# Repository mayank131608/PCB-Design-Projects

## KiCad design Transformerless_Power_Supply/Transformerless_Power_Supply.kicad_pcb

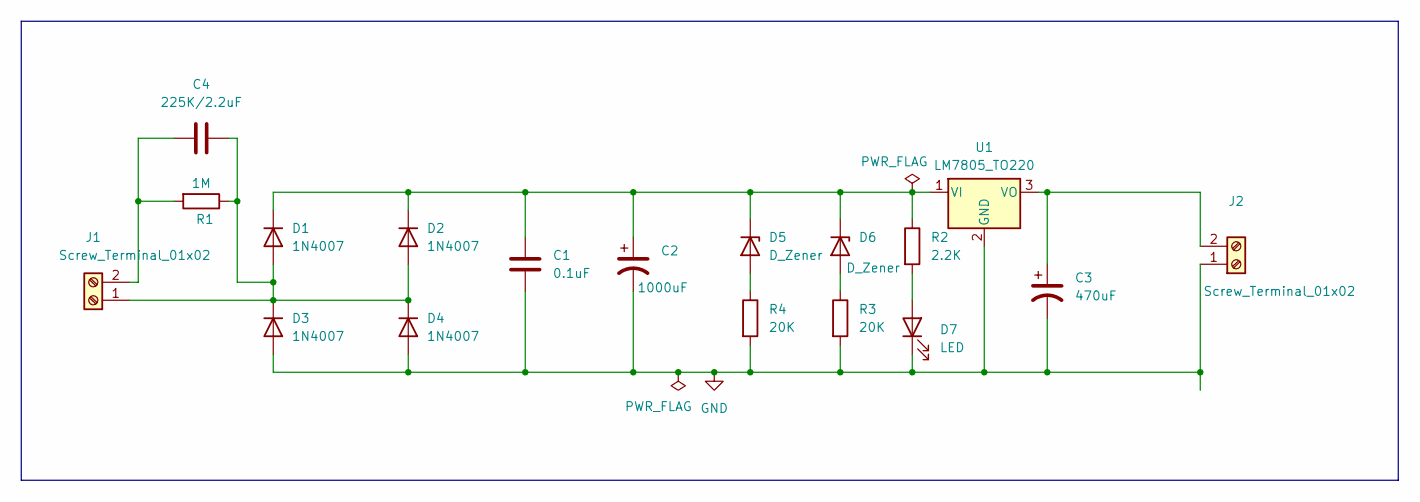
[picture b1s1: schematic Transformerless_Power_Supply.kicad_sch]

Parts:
C1: 0.1uF; C_Disc_D4.7mm_W2.5mm_P5.00mm
C2: 1000uF; CP_Radial_D10.0mm_P5.00mm
C3: 470uF; CP_Radial_D10.0mm_P3.80mm
C4: 225K/2.2uF; C_Rect_L18.0mm_W6.0mm_P15.00mm_FKS3_FKP3
D1, D2, D3, D4: 1N4007; D_DO-41_SOD81_P10.16mm_Horizontal
D5, D6: D_Zener; D_A-405_P7.62mm_Horizontal
D7: LED; LED_D5.0mm
J1, J2: Screw_Terminal_01x02; TerminalBlock_bornier-2_P5.08mm
R1: 1M; R_Axial_DIN0207_L6.3mm_D2.5mm_P7.62mm_Horizontal
R2: 2.2K; R_Axial_DIN0207_L6.3mm_D2.5mm_P7.62mm_Horizontal
R3, R4: 20K; R_Axial_DIN0207_L6.3mm_D2.5mm_P7.62mm_Horizontal
U1: LM7805_TO220; TO-220-3_Vertical

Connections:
GND: C1.2, C2.2, C3.2, D3.2 (A), D4.2 (A), D7.1 (K), J2.1, R3.2, R4.2, U1.2 (GND)
unnamed: C4.2, D1.2 (A), D2.2 (A), D3.1 (K), D4.1 (K), J1.1, R1.1
unnamed: C1.1, C2.1, D1.1 (K), D2.1 (K), D5.1 (K), D6.1 (K), R2.1, U1.1 (VI)
unnamed: D5.2 (A), R4.1
unnamed: D6.2 (A), R3.1
unnamed: D7.2 (A), R2.2
unnamed: C4.1, J1.2, R1.2
unnamed: C3.1, J2.2, U1.3 (VO)

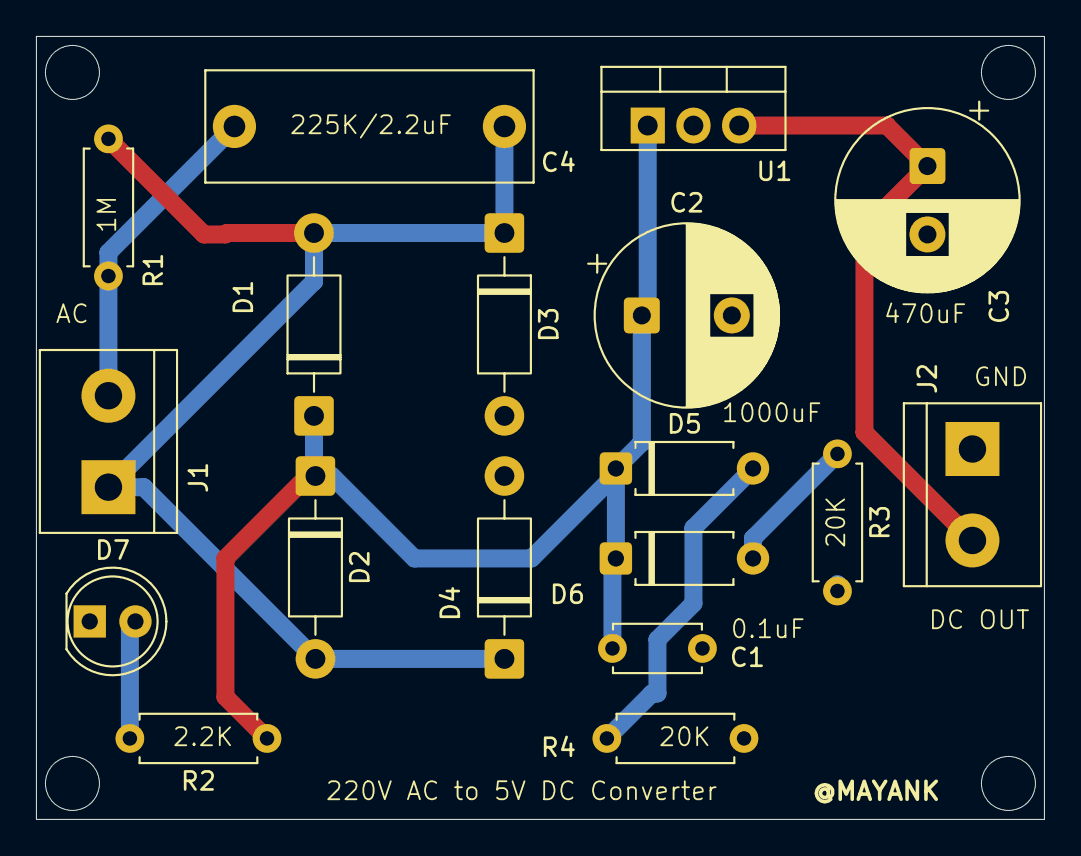
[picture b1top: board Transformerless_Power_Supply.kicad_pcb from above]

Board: 2 copper layers, 56.0 x 43.5 mm, 18 parts (0 on the bottom side), 8 nets.

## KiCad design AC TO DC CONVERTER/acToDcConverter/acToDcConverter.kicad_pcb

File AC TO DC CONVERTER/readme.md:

# AC to DC Converter PCB (Bridge Rectifier Power Supply)

A beginner-friendly PCB design of a **linear AC to DC power supply** created using KiCad.
This project converts low-voltage AC from a step-down transformer into filtered DC output using a full bridge rectifier and smoothing capacitor.

> ⚠️ This circuit is designed for transformer output (9–15VAC).
> **DO NOT connect directly to 230V mains.**

---

## 📌 Features

* Full bridge rectifier using 1N4007 diodes
* Ripple filtering using electrolytic capacitor
* Power indication LED
* Screw terminal input/output connectors
* Single layer PCB (easy to manufacture)
* 3D modeled board

---

## 🧠 Working Principle

1. AC voltage from a step-down transformer enters through input terminal
2. Four diodes form a bridge rectifier converting AC → pulsating DC
3. Electrolytic capacitor smooths ripple and produces DC
4. LED indicates output presence
5. DC available at output terminal

[
V_{DC} ≈ 1.414 × V_{AC(rms)} − 2V_d
]

Example:
12VAC → ~15–17V DC (no load)

---

## 🗂️ Files Included

| File       | Description         |
| ---------- | ------------------- |
| Schematic  | Circuit diagram     |
| PCB Layout | Routed PCB          |
| 3D Model   | Board preview       |
| Gerbers    | Manufacturing files |

---

## 🔧 Components Used

| Component | Value                         |
| --------- | ----------------------------- |
| D1–D4     | 1N4007 Diodes                 |
| C1        | 1000µF Electrolytic Capacitor |
| R1        | 10kΩ                          |
| R2        | 2.2kΩ                         |
| D5        | LED                           |
| J1, J2    | Screw Terminals               |

---

## 📤 Output Voltage

| AC Input | Approx DC Output |
| -------- | ---------------- |
| 9VAC     | ~12V             |
| 12VAC    | ~16V             |
| 15VAC    | ~20V             |

*(varies with load)*

---

## ⚠️ Safety

* Use **only transformer isolated AC**
* Do not connect mains supply
* Not a regulated power supply
* Output voltage changes with load

---

## 🛠️ Designed With

* KiCad (Schematic & PCB)
* KiCad 3D Viewer

---

## 🎯 Learning Objectives

This project helped me learn:

* Bridge rectifier design
* Capacitor filtering
* PCB routing for power circuits
* Footprints & 3D modeling
* Basic power electronics layout rules

---

## 🚀 Future Improvements

* Add voltage regulator (7805 / 7812)
* Add fuse protection
* Add reverse polarity protection
* Add heatsink support

---

## 👨‍💻 Author

**Mayank Pandey**, 
Electronics Engineering Student, 
HBTU KANPUR

---

⭐ If you found this useful, feel free to star the repository!

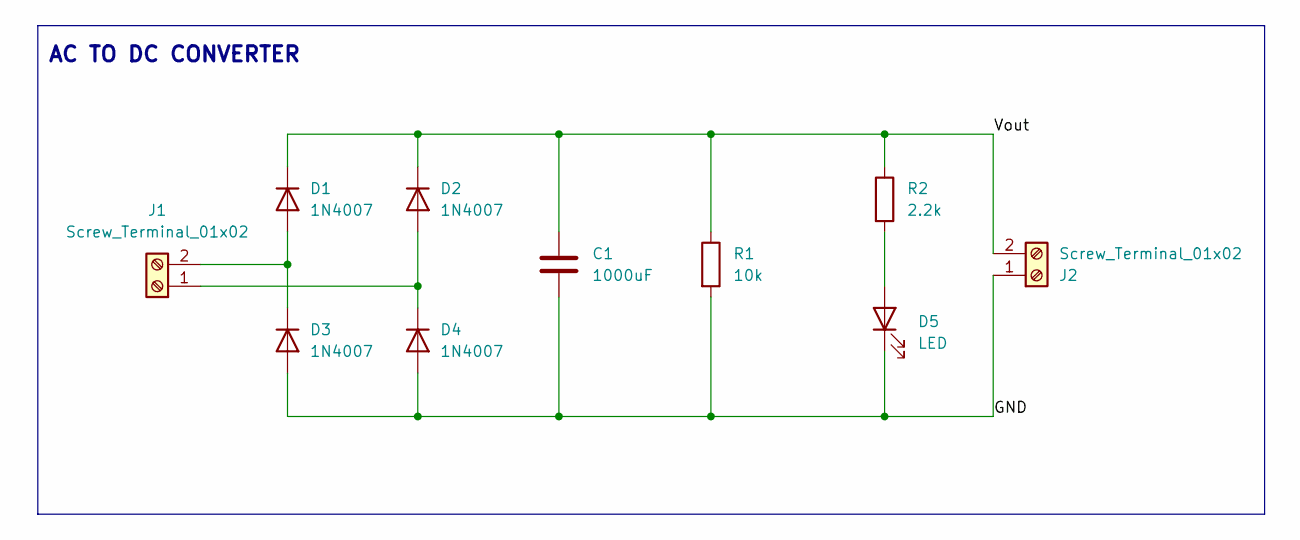
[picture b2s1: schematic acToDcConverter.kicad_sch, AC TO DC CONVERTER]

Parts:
C1: 1000uF; C_Disc_D8.0mm_W2.5mm_P5.00mm
D1, D2, D3, D4: 1N4007; D_DO-41_SOD81_P10.16mm_Horizontal
D5: LED; LED_D5.0mm
J1, J2: Screw_Terminal_01x02; TerminalBlock_bornier-2_P5.08mm
R1: 10k; R_Axial_DIN0207_L6.3mm_D2.5mm_P7.62mm_Horizontal
R2: 2.2k; R_Axial_DIN0207_L6.3mm_D2.5mm_P7.62mm_Horizontal

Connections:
/GND: C1.2, D3.2 (A), D4.2 (A), D5.1 (K), J2.1, R1.2
/Vout: C1.1, D1.1 (K), D2.1 (K), J2.2, R1.1, R2.1
unnamed: D1.2 (A), D3.1 (K), J1.2
unnamed: D2.2 (A), D4.1 (K), J1.1
unnamed: D5.2 (A), R2.2

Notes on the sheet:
AC TO DC CONVERTER

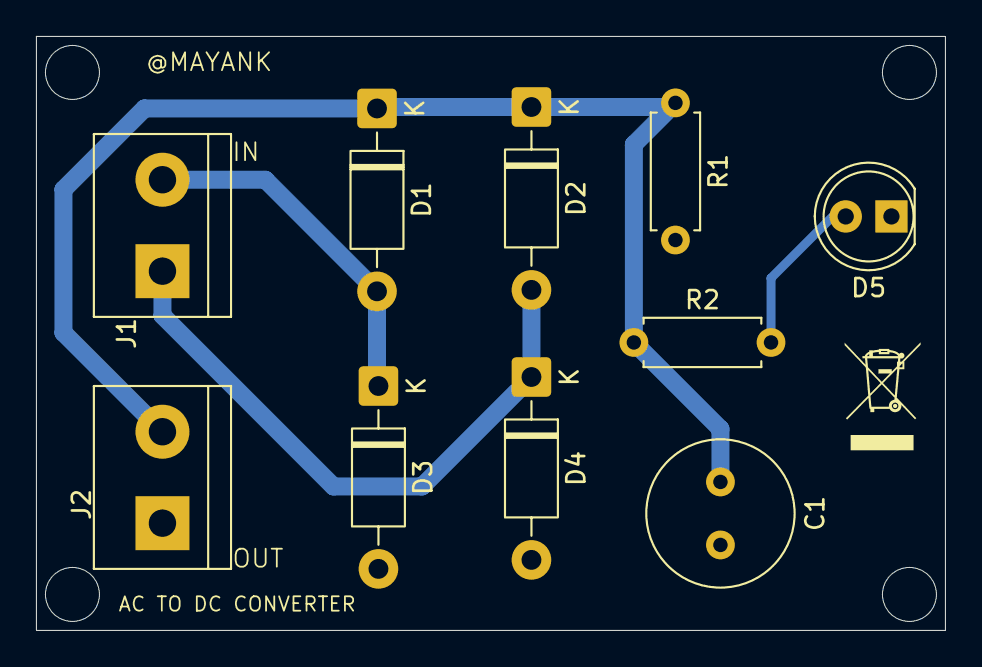
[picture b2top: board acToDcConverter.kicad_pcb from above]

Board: 2 copper layers, 50.5 x 33.0 mm, 10 parts (0 on the bottom side), 5 nets.

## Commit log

2026-02-21 Add readme for AC to DC converter project
    Added a detailed readme for the AC to DC converter project, including features, working principle, components used, output voltage, safety precautions, and future improvements.
